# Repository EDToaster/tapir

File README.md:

# Keyboard projects

| Project | What it is | Status |
| --- | --- | --- |
| [Tapir](tapir/) | Flat wireless 42-key split keyboard with a thumb pointing stick | Rev A digital prototype, on hold |
| [TMR half](tmr-half/) | 28-key half-size analog keyboard with TMR sensors and rapid trigger | Rev A test coupon rebuilt for second review, not ordered |

Shared [silkscreen patterns](silkscreen-patterns/) hold generative artwork for any board here.

Each project has its own README and AGENTS.md. Run Tapir's commands from `tapir/`.

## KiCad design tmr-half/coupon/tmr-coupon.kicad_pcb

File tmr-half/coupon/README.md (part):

# TMR half test coupon, rev A

A 2 × 3 key test board for the [TMR half](../README.md) keyboard. It carries the same sensor cell, the same multiplexer and the same sensor power switch that the 28-key board would use, so the open questions in [design-decisions.md](../design-decisions.md) can be answered with measurements before the full board is drawn.

**Status: rev A rebuilt for second review; not ordered.** The CAD and CAM gates pass. Nothing has been measured on hardware. Ordering needs the owner's approval ([AGENTS.md](../AGENTS.md)).

The schematic is [tmr-coupon.kicad_sch](tmr-coupon.kicad_sch) ([picture](docs/schematic.png)). The board is [tmr-coupon.kicad_pcb](tmr-coupon.kicad_pcb). Both open in KiCad 10.

## What it tests

| Question | How the coupon answers it |
| --- | --- |
| How strong is the field at rest and at bottom-out? | Six sensor cells at the Partial-Gauss position. T1 compares 1.2 mm and 1.6 mm boards and checks the margin for 0.500 and 0.75 sensitivity. |
| Is the cheap 74HC4067 fast enough? | Both muxes are the CD74HC4067SM96 proposed in D7, wired the way the full board would be. |
| How much does the bypass capacitor matter? | Rail A (K1–K3) has the datasheet 100 nF per sensor. Rail B (K4–K6) has 10 nF. |
| Does the optional output capacitor help or hurt? | K2 and K5 have 100 pF on the sensor output. Their neighbours have empty pads. |
| What does pulsing the sensor power cost? | Each rail has a switch, a 10 Ω current shunt and a voltage monitor. T6 checks when a key reading becomes valid after power-on. |
| Does an RC filter in front of the ADC help? | 0 Ω links and empty capacitor pads sit at both ADC inputs. |
| Does the optional battery path work? | The JST-PH connector feeds the module's B+ pad through Q3 and a slide switch. A warning LED is connected on the battery side of both. |

## How the circuit works

A short tour for someone new to analog circuits.

- **Sensor cell.** Each key has one TMR2617S on the bottom of the board, 4.40 mm south of the switch centre. It has three pins: supply, ground, and an output voltage that moves as the magnet in the switch comes closer. A small capacitor next to it steadies its supply.
- **Multiplexer.** The controller only has three free analog inputs, so a 16:1 analog switch (U7, U8) picks one sensor at a time and connects it to one ADC pin. Four select lines S0–S3 carry a binary address from 0 to 15. Both muxes share the select lines, so both muxes present their selected inputs at once. The SAADC samples the two inputs sequentially.
- **Channel map.** Key inputs on each mux are separated by grounded inputs. Key and ground addresses: Addresses 1, 3 and 5 carry K1/K2/K3 on A and K4/K5/K6 on B. Addresses 0, 2, 4, 6 and 8–15 read ground. Rail-monitor addresses: Both monitors use address 7. Grounded addresses give a zero reading for offset and settling tests.
- **Rail switch.** Q1 and Q2 are P-channel MOSFETs between the module's 3.3 V pin and the two sensor rails. Each 100 kΩ gate pull-down keeps its rail on by default. A high on PWR_A_N or PWR_B_N turns that rail off.
- **Shunt.** Each rail has a 10 Ω current-sense resistor. A reading of 1 mV across it means 100 µA. The expected steady drop is up to about 11 mV: three sensors at up to 300 µA each plus 3.3 V / 20 kΩ = 165 µA for the monitor, or 1.065 mA × 10 Ω = 10.65 mV at nominal values ([MDT datasheet, p. 4](https://www.dowaytech.com/en/res/202408/21/dd53d68876041b0f.pdf), **drawing** plus calculation).
- **Rail monitor.** Two 10 kΩ resistors halve each sensor rail into its MON channel. Use the monitor from the same rail and ADC channel as the key. After subtracting the ground reading from each, divide the key reading by twice the MON reading to get Vout / Vsensor. Sample them close together with the rail on and stable. Skip the calculation if MON is near zero. See [Supply and reference](../analog-readout.md#supply-and-reference).
- **ADC filter pads.** R11 and R12 are 0 Ω links and C19 and C20 are empty. Swap in a resistor and capacitor to try a filter without a new board.

## Pin map

Controller pads as seen from the top with USB at the top edge. Pin names follow the [nice!nano v2 pinout](https://nicekeyboards.com/docs/nice-nano/pinout-schematic/).

| Signal | nRF pin | Pro Micro name | Notes |
| --- | --- | --- | --- |
| S0, S1, S2, S3 | P0.17, P0.20, P0.22, P0.24 | D2, D3, D4, D5 | Mux address, S0 is the low bit |
| MUX_EN_N | P1.00 | D6 | Low enables both muxes. Pulled low by R13, so it can be left alone. |
| PWR_A_N | P0.11 | D7 | High turns rail A off. Leave floating or low for always on. |
| PWR_B_N | P1.04 | D8 | High turns rail B off. Use standard drive and low-frequency switching per the [Nordic pin table](https://docs.nordicsemi.com/r/bundle/ps_nrf52840/page/pin.html) (**drawing**). |
| AIN_A | P0.02 / AIN0 | | Mux A output (K1–K3) |
| AIN_B | P0.29 / AIN5 | | Mux B output (K4–K6) |
| AIN_SPARE | P0.31 / AIN7 | | Only goes to J3 pin 8. Configure as an output driven low when unused. |
| VCC | 3.3 V pin | | Supplies the muxes and both rail switches |
| B+ | battery pin | RAW position | From J1 through Q3 and S1. Verify B+ on your actual clone. |

Debug header J3 is vertical, pad 1 nearest the top edge. In pad order: GND, 3V3, SWA (before A shunt), VSA (after A shunt), SWB, VSB, S0, A7, MXB, MXA. The labels are on the bottom.

J3 is an exposed bench header, without added ESD protection or a fuse. Clip ground first and attach insulated probes with power off. Do not bridge 3V3 or either rail to a mux output; never drive J3 pin 8 while P0.31 is driving it low. Rev A has no S0–S3 pulls. While those GPIOs are high-impedance (reset, bootloader, or sleep modes that release them), the mux channel is undefined and floating input levels can increase supply current. Drive the selects to a known level before sampling and park them before sleep if the GPIO state is retained. Full-board pull-downs are Proposed in D19.

## Layout

| Item | Value |
| --- | --- |
| Board | 92 × 50 mm, 2 layers, 2 mm corner radius (**drawing**). T1 compares nominal 1.2 mm and 1.6 mm. |
| Keys | 19.05 mm pitch, 3 columns × 2 rows |
| Assembled parts | One-sided assembly on the bottom. 42 placements. |
| Hand-fitted | Controller on the top, six switches pressed in from the top |
| Mounting | Four M2 holes at 3 mm from each corner |
| Antenna | No copper on either layer under the controller's antenna end |
| Battery | J1 opens toward the bottom edge. S1's lever extends 1.00 mm past the edge and its body stops 0.50 mm short (nominal drawing geometry). |
| Decoration | Quadtree Truchet pattern on both silkscreen layers, see [Decorative silkscreen](#decorative-silkscreen) |

Use the same design at both thicknesses for T1. Gateron shows the sensor under a 1.20 mm PCB beside a 1.20 ± 0.05 mm mechanical dimension ([KS-33D drawing, p. 7](https://www.gateron.com/u_file/2603/10/file/GATERONLowProfileMagneticJadeProSwitch-KS-33DD10B060NW-D276.pdf), **drawing**). JLCPCB's [rigid PCB capabilities](https://jlcpcb.com/capabilities/pcb-capabilities) list ±10% thickness tolerance at 1.0 mm and above, so measure the bare edge of each finished board. The switches use locating posts, the battery connector and slide switch are surface mounted, and ordinary soldered headers and M2 fasteners can be sized for either board. Dry-fit everything. Check that the switch bodies sit flat, header pins protrude far enough to solder, locator pegs do not foul the mounts and M2 screws engage without bottoming out. Retention without a plate is still untested.

Design rules used, against [JLCPCB's published limits](https://jlcpcb.com/capabilities/pcb-capabilities) for 2-layer 1 oz boards:

| Rule | This board | JLCPCB minimum |
| --- | --- | --- |
| Track width | 0.20 signal class, 0.40 power class, 0.15 absolute minimum; five signal segments below class width | 0.10 |
| Clearance | 0.20 | 0.10 |
| Via | 0.60 pad, 0.30 hole | 0.25 pad, 0.15 hole |
| Copper to board edge | 0.30 DRC; 0.4000 pour, 0.5273 track, 0.5350 via, 0.4350 pad (generated Gerber to routed centreline) | 0.20 fabrication; >0.30 for Economic assembly traces |
| Copper to unplated hole | 0.30 | 0.20 |
| Silkscreen text height | 1.0 | 1.0 |
| Silkscreen line width | 0.15 text strokes; 0.30 thinnest pattern feature | 0.15 |
| Silkscreen to pad | 0.30 for the pattern | 0.15 |

Round 2 reused the reviewed route, with no signal copper moved. The [analog layout report](reports/analog-layout.json) measures track and via proximity from 21 aggressors (address/control, reset, battery, rails, gates and MON), including MON and AIN_SPARE as victims. A sensor's own supply near its VCC pad is reported separately within a 1.5 mm escape radius (**allowance**). The existing rail/MON proximities, the 12.054 mm MUXB/RST and 5.239 mm OUT3/VCC opposite-layer parallel spans are retained and reported; do not sample during reset or VCC transitions. T2–T4 still have to measure the actual effect. These geometry checks are not a prediction of coupled noise.

In the close-track metric (**measured** by the repository gate from KiCad geometry), AIN_SPARE runs 2.221 mm within 0.50 mm of S1, at a minimum edge gap of 0.2105 mm. AIN_SPARE/MUXB have 0.648 mm of close same-layer run and a 0.2274 mm via proximity. MUXA/MUXB have no close same-layer track run, 0.744 mm of opposite-layer parallel overlap and a 0.3071 mm closest via proximity. These track/via numbers exclude component lands; the review's 5.7 mm segment tally near J3 and R11 is an upper bound, not projected parallel length.

Three nets meet the unchanged 80% opposite-layer ground coverage goal. The regression floors give roughly three percentage points of headroom below achieved coverage; they are not design targets.

| Net | Original coverage (%) | Rev A coverage (%) | Regression floor (%) |
| --- | ---: | ---: | ---: |
| OUT1 | 74.0 | 67.7 | 64 |
| OUT2 | 52.9 | 60.8 | 57 |
| OUT3 | 45.2 | 85.0 | 82 |
| OUT4 | 42.4 | 78.9 | 75 |
| OUT5 | 31.5 | 100.0 | 97 |
| OUT6 | 48.0 | 80.8 | 77 |
| MUXA | 55.3 | 47.2 | 44 |
| MUXB | 54.5 | 65.9 | 62 |
| AIN_A | 0.0 | 58.9 | 55 |
| AIN_B | 0.0 | 59.1 | 56 |

The generated board has 97 two-sided ground stitching vias, two front/eight back filled regions and at least two ties per region. All 17 critical ground pads touch local pour; their longest distance to a through stitch is 1.05 mm. Of 336.369 mm of retained GND trace, 44.313 mm of centreline lies outside a same-layer pour. The fill minimum is 0.20 mm on both layers; the first substantial split in the erosion screen is at 0.240 mm front and 0.200 mm back. These are CAD measurements and a geometry screen, not measurements of etching or electrical performance. T2 through T4 still need physical measurements.

The [mechanical report](reports/mechanical.json) measures 0.3058 mm from the closest sensor land to the Ø5.2 mm hole and a 0.40 mm minimum battery trace width on all three battery positive nets. Mux bypass supply pad centres are 1.75 mm apart; the corresponding ground pad centres are 12.578 mm apart. Both grounds reach local pour and stitching; those distances do not measure the electrical loop length.

## Parts

The full list with part numbers is [bom.csv](bom.csv). The files JLCPCB needs are in [fab/](fab).

| Refs | Part | LCSC | JLC class |
| --- | --- | --- | --- |
| U1–U6 | MDT TMR2617S-AAC-0.500-500, SOT-23-3 | [C55130211](https://www.lcsc.com/product-detail/C55130211.html) | Extended |
| U7, U8 | TI CD74HC4067SM96, SSOP-24 | [C98457](https://www.lcsc.com/product-detail/C98457.html) | Extended |
| Q1–Q3 | AO3401A P-MOSFET, SOT-23 | C15127 | Basic |
| J1 | JST S2B-PH-SM4-TB(LF)(SN) | C295747 | Extended |
| S1 | C&K PCM12SMTR, 300 mA at 6 V DC | [C221841](https://jlcpcb.com/partdetail/CK-PCM12SMTR/C221841) | Extended |
| D1 | KENTO KT-0603R red warning LED | [C2286](https://jlcpcb.com/partdetail/C2286) | Basic |
| R15 | 1 kΩ 0603WAF1001T5E | [C21190](https://jlcpcb.com/partdetail/C21190) | Basic |
| C1–C3, C7, C8 | 100 nF 0603 | C14663 | Basic |
| C4–C6 | 10 nF 0603 | C57112 | Basic |
| C12, C15, C17, C18 | 100 pF C0G 0603 | C14858 | Basic |
| C9 | 1 µF 0603 | C15849 | Basic |
| R1, R2 / R3, R4 / R5, R6 | 100 Ω / 100 kΩ / 10 Ω 0603 | C22775 / C25803 / C22859 | Basic |
| R7–R10, R13 / R11, R12 | 10 kΩ / 0 Ω 0603 | C25804 / C21189 | Basic |

Not fitted on purpose: C11, C13, C14, C16 (output capacitor positions) and C19, C20 (ADC filter capacitors). Paste intentionally remains on these pads for later hand fitting.

You supply and fit by hand:

- The nice!nano v2 clone.
- Six Gateron Low Profile Magnetic Jade Pro switches. [NuPhy](https://nuphy.com/products/gateron-low-profile-magnetic-jade-pro-switches) sells them in packs of 70 or 90.
- Four brass or nylon M2 standoffs and screws. Start with 8 mm or taller (**allowance**). Avoid steel near the magnets. From board coordinates, the nearest mounting hole is H1, 15.207 mm centre-to-centre from K1. The closest S1/J1 metal mounting-land centre is 18.742 mm from K6. This is a PCB measurement, not a magnetic field measurement.
- Optional: a 1-cell LiPo with a JST-PH plug such as [Adafruit 1578](https://www.adafruit.com/product/1578), keycaps, and a 10-pin header for J3.

### Sensor stock

On 2026-11-27, [JLCPCB C55130211](https://jlcpcb.com/partdetail/58850683-TMR2617S_AAC_0_500500/C55130211) showed zero stock, Extended, with a minimum buy of 18. At its displayed estimate of $0.5015 each, 18 cost about $9.03 before any fees or tax. [LCSC C55130211](https://www.lcsc.com/product-detail/C55130211.html) also showed out of stock, with minimum 1, multiple 1, and a reference price of $0.4989 for one. Recheck both listings and the price before buying.

For a fully assembled coupon, pre-order C55130211 in the JLCPCB Parts Library. Wait until your library shows enough available parts for the boards and any assembly allowance shown by JLCPCB. Each board uses six sensors. Eighteen pieces may be insufficient for two assembly orders. JLCPCB keeps pre-ordered parts for PCBA and does not ship them separately. Lead time is unconfirmed.

If you choose to hand-solder the sensors, deselect U1–U6 in the assembly BOM. Source the exact TMR2617S-AAC-0.500-500 from LCSC if it returns to stock, or verify the SOT-23-3 package, 0.500 mV/V/Gs sensitivity and 500 mV/V offset before using [Calero's programmed-to-order TMR2617S option](https://tmr-sensors.com/products/tmr2617). Confirm lead time and total cost before placing a board order. Pins 1 and 2 have 1.10 × 0.60 mm lands and 0.20 mm nominal toe. Pin 3 has a 1.45 × 0.60 mm land and 0.55 mm nominal toe. The toe is calculated from PCB dimensions and the MDT p. 6 lead span. Use a fine tip beside the center hole.

### Decorative silkscreen

Both sides carry a crop of the [quadtree Truchet pattern](../../silkscreen-patterns/) (pattern 03), enlarged so the lines print thicker. It is cosmetic and connects to nothing.

| Item | Value |
| --- | --- |
| Source | `silkscreen-patterns/svg/03_quadtree_truchet.svg`, 400 × 250 mm |
| Zoom | 2×, so the board shows a 46 × 25 mm window of the source |
| Window, top side | Top-left corner at (90, 95) mm in the source |
| Window, bottom side | Top-left corner at (300, 150) mm in the source |
| Stroke widths | 0.78, 1.56 and 2.80 mm (source strokes 0.39, 0.78 and 1.40 mm, **drawing**) |
| Ink | 247.5 mm² in 20 areas on top, 392.2 mm² in 24 areas on the bottom (generated-board measurement) |

Every functional mark takes priority over the pattern. [tools/silk_pattern.py](tools/silk_pattern.py) turns the strokes into filled areas and cuts away anything closer than these distances:

| Kept clear of | Distance (**allowance**) |
| --- | --- |
| Pads, holes, part courtyards and silkscreen lines | 0.30 mm |
| Text labels | 0.45 mm around the label's box |
| Board edge | 0.60 mm |
| M2 mounting holes | The 5.1 mm screw-head courtyard plus 0.30 mm, on both sides |

Gaps between keepouts narrower than 1.0 mm stay empty. Leftover pieces thinner than 0.30 mm, smaller than 4 mm² or shorter than 4.5 mm are dropped. [tools/check_silk.py](tools/check_silk.py) measures the decorative ink on the routed board: 0.299 mm from the closest pad, hole or mark (the 0.30 mm target less polygon rounding) and 0.625 mm from the board edge ([decoration report](reports/silk-clearance.json)). The plotted legend as a whole comes within 0.345 mm on top and 0.425 mm on the bottom ([Gerber read-back](reports/gerber-silk.json)).

Two things to know:

- The six front 14 × 14 mm seating squares exclude all legend ink. The LED cues are outside them.
- Vias are tented. The [silk read-back report](reports/gerber-silk.json) measures 10 via holes under plotted ink on the top and 18 on the bottom.

To change the look, edit `ZOOM` or `CROP` in `silk_pattern.py` and run `tools/build.sh`. Copper is untouched, so no reroute is needed.

## Ordering at JLCPCB

Wait for the owner's approval before buying anything. The proposed comparison is one assembled batch at nominal 1.2 mm and one at 1.6 mm. A cheaper option is one assembled thickness plus bare boards at the other thickness. Populate at least one bare board with the same parts and capacitor options before comparing. Choose at order time.

1. Upload `fab/tmr-coupon-revA-gerbers.zip` for each thickness. Confirm the detected 92 × 50 mm outline and two layers (**drawing**).
2. Set the chosen thickness. [JLCPCB Economic PCB Assembly capabilities](https://jlcpcb.com/capabilities/pcb-assembly-capabilities) list both thicknesses for a single board of this size. Choose green solder mask and explicitly select lead-free HASL if available for both thicknesses (Proposed); use the same finish and mask for the comparison. Choose “Order Number (Specify Position)” if using the bottom-side placeholder.
3. Turn on Economic PCB Assembly and select **Bottom Side** for the assembled batch or batches. Two or five boards per assembled batch fit the published two-layer green/HASL options.
4. Upload `fab/tmr-coupon-revA-bom-jlc.csv` and `fab/tmr-coupon-revA-cpl-jlc.csv`. Check the fitted lines match the exported BOM: 16 BOM lines.
5. For a complete assembly, stop unless the sensors are available in the JLCPCB parts library for your order. See [Sensor stock](#sensor-stock).
6. Inspect the placement preview before paying. Check mux pin 1 at the triangles, sensors and MOSFETs on the right pads, the warning LED polarity, and the J1 opening and S1 lever toward the edge. Confirm S1's two pegs centre over the two Ø0.90 mm holes and the sensor bodies centre 4.40 mm south of their switch centres (**drawing**). The offline CPL gate is not a substitute for this preview.
7. Account for the edge conflict. S1's body is 0.50 mm inside the nominal routed edge, but its lever overhangs by 1.00 mm; J1 mates toward the same edge. The [Economic FAQ](https://jlcpcb.com/help/article/pcb-assembly-faqs-part-2) asks for more than 0.30 mm clearance for traces and components and quotes about 0.20 mm routing tolerance; the [assembly terms](https://jlcpcb.com/help/article/terms-and-conditions-of-jlcpcb-assembly-service) call for at least 2.5 mm for component bodies. A copper-rule pass does not clear the assembly envelope. Plan for one of three outcomes: an engineering query/hold for Economic assembly, Standard assembly with removable rails and actuator clearance, or deselect S1 in the assembly order and hand-fit it after depaneling.
8. Review the tooling and final production file. The [after-sales FAQ](https://jlcpcb.com/help/article/common-pcba-after-sales-issues-and-faq) says Economic assembly typically adds two or three Ø1.152 mm NPTH tooling holes near the corners. Use blank corner locations where possible; corner copper is ground only, not a licence to cut a stitch, interfere with an M2 hole, or cut live copper elsewhere. Confirm the tooling holes, rails, fitted part list and placement/polarity in the live production file under Order History before release. Do not assume it matches the preview.

### Before you pay

- **Sensor supply:** Verify enough of C55130211 for the order and assembly allowance, or choose the documented hand-solder route. Do not rely on a stock snapshot.
- **Thickness:** Choose the D12 plan for the 1.2 mm and 1.6 mm comparison, with matching parts, mask and finish.
- **Edge assembly:** Accept the S1 overhang risk and choose an assembly fallback. Check the new tooling holes and how any rails clear the actuator and J1.
- **Battery:** Accept that reverse pack + USB + S1 on remains unprotected. Use the first-connection procedure each time and accept the Proposed D18 LED limitation separately.
- **Test firmware:** Plan the bare-metal T3/T6 timing test; it is not implemented, and the ZMK sketch does not replace it.
- **Clone checks:** Verify B+, VCC and P0.13 on the actual controller before soldering.
- **Placement:** Complete step 6, including both S1 pegs and all six sensor centres; confirm the final production file when available.
- **Ground reference:** Accept 47.2% under MUXA and 65.9% under MUXB as coupon limits, not full-board targets.
- **Extended fees:** Check the live quote for all four Extended lines (sensors, S1, muxes and J1). No fee amount has been verified.

## Assembly and bring-up

### Check your clone before soldering

1. Find the clone's B+ from its pinout or schematic. Compare the physical pad against the coupon footprint with USB pointing toward the same edge. Use continuity with all power removed if you need to confirm a connection. The RAW position alone does not identify a battery input.
2. Power the loose module from USB, with no battery. Measure its 3.3 V/VCC pin against GND and record the voltage. Keep the probes from bridging adjacent pads.
3. With test firmware on the loose module, drive P0.13 high and low and measure VCC in each state. ZMK's [genuine nice!nano v2 board file](https://github.com/zmkfirmware/zmk/blob/main/app/boards/nicekeyboards/nice_nano/nice_nano_nrf52840_zmk_2_0_0.overlay) enables VCC with P0.13 high (**drawing**). Verify your clone's behavior before using the pin. Leave external power enabled for the coupon. If B+ or VCC does not match the footprint, stop before soldering.

### Assembly

1. Inspect the bottom side. U7 and U8 pin 1 at the triangle. No solder bridges on the mux pins.
2. With nothing else attached, measure resistance between J3 pin 1 (GND) and pin 2 (3V3). It should not read as a short.
3. Solder the controller on the top side with its chips facing up and USB at the board edge. Pad 1 (square) is P0.06. Sockets or pin headers are fine.
4. Press the switches in from the top with the LED windows toward the LED marks. With no plate, the locating posts can let a switch lift or tilt. Keep each housing flat against the board, press straight down, and check that it returns to its seat. If needed, hold the housing down from its sides or tack it with removable tape away from the seating surface. Use the same method for both thicknesses.
5. Fit standoffs.
6. Plug in USB. Measure 3.3 V between GND and 3V3 on J3, and about 3.3 V on VSA and VSB.
7. Measure across each shunt from its switch side to its sensor side. Expect up to about 11 mV steady state with the rails on. See the shunt calculation above. On J3, measure SWA (3) minus VSA (4), or SWB (5) minus VSB (6).

### Optional battery

Use a compatible single-cell LiPo. Leave the module's charge-boost jumper open. The genuine nice!nano normally charges at about 100 mA and its boost setting is about 500 mA ([nice!nano FAQ](https://nicekeyboards.com/docs/nice-nano/faq/) and [battery guidance](https://nicekeyboards.com/docs/nice-nano/)). The [documented SuperMini version](https://wiki.icbbuy.com/doku.php?id=developmentboard:nrf52840) lists 100 mA normally and 300 mA with boost. Check both the module and the battery manufacturer's allowed charge current before using battery power. The switch is C&K PCM12SMTR, rated 300 mA at 6 V DC ([manufacturer datasheet, pp. 1–2](https://www.littelfuse.com/assetdocs/littelfuse-ck-slide-pcm-series-datasheet?assetguid=d2f6a96c-7a9a-4c4e-a5aa-4fe3075dffe5), **drawing**); 300 mA would use its entire current rating and 500 mA exceeds it. [JLCPCB C221841](https://jlcpcb.com/partdetail/CK-PCM12SMTR/C221841) showed 7,232 in stock, Extended, minimum one on 2026-11-27.

1. Unplug USB. Set S1 to OFF. Verify the lever positions at the switch terminals with continuity while the board is unpowered. Compare the loose pack contacts with the connector's `+` marking using a meter. JST-PH plugs come wired in both polarities ([SparkFun JST-PH guide](https://learn.sparkfun.com/tutorials/single-cell-lipo-battery-care/jst-ph-connectors)).
2. With USB still unplugged and S1 still OFF, plug in the pack. The reverse-polarity warning LED must stay dark. If it lights, unplug the pack and stop.
3. Confirm with a meter that J1 pin 1 is positive relative to board GND, using accessible pads or test points. A dark LED alone does not prove correct polarity. If the reading is missing, negative or unclear, unplug the pack and investigate. Switch on only after a positive meter reading.

To check that the `POLARITY` LED works, use no battery, unplug USB and set S1 OFF. Use a floating bench supply set to 3.0 V with a 3 mA current limit (**test allowance**). With its output off, connect supply positive to board GND (J1.2) and negative to J1.1. Briefly enable the output and verify that D1 lights; disable it and disconnect both leads before attaching a pack or USB. If it does not light, stop and inspect D1, R15 and the connections. Never intentionally reverse a real pack. A dark LED does not prove correct polarity: use the meter check above.

The D1 indicator (KT-0603R) anode goes to GND and its cathode goes through R15 (1 kΩ) to raw J1 pin 1. That lets it light with a reversed pack even while S1 is off. With a reversed 3.0–4.2 V pack the current is roughly 1–2.5 mA (estimate). A correctly connected fully charged 4.2 V pack reverse-biases D1 continuously, even with S1 OFF: 0.8 V below its 5 V absolute maximum, not a lifetime guarantee. [KENTO, pp. 2–3](https://www.lcsc.com/datasheet/lcsc_datasheet_1810231112_Hubei-KENTO-Elec-KT-0603R_C2286.pdf) specifies up to 5 µA reverse leakage at 5 V and 25 °C (**datasheet test condition**, not a measured 4.2 V drain or a hot limit). No extra diode in rev A. Continuous reverse bias, off-state drain and silent indicator failure are limits proposed for owner acceptance in D18.

| Pack and power state | Expected behavior |
| --- | --- |
| Correct pack, S1 on, USB absent | The pack starts powering the module through Q3's body diode. Q3 then turns on and carries the battery current with less voltage drop. |
| Correct pack, S1 on, USB present | The module can charge the pack through the turned-on Q3. Leave boost open and check the pack's allowed charging current. |
| Reversed pack, USB absent | Q3 normally blocks the negative pack voltage from B+. Its body diode is reverse-biased. The warning LED can light with S1 in either position. |
| Reversed pack, USB present, S1 off | S1's open throw isolates the charger B+ path. The raw-pack warning LED can still light. Do not intentionally test a reversed pack with USB attached. |
| Reversed pack, USB present, S1 on | The charger can raise B+ and turn Q3 on. Current can then flow from the charger through Q3 toward the reversed pack. The charger and the impedances of the module, pack and wiring affect that current. No safe current or Q3 dissipation can be claimed for this fault. |
| No pack, USB present | The module should run from USB. Keep S1 off before fitting a pack. With S1 on, some chargers may put voltage on the empty battery connector through Q3. |

Q3 is an AO3401A. Pin 1 is gate, pin 2 source and pin 3 drain; its body diode points from the raw-pack drain toward the switch-side source ([AOS datasheet, pp. 1–2](https://www.aosmd.com/sites/default/files/res/datasheets/AO3401A.pdf), **drawing**). Once on, a 3.0 V cell gives roughly −3.0 V gate-to-source drive. The datasheet specifies up to 85 mΩ at −2.5 V under its room-temperature test condition, equivalent to about 8.5 mV at 100 mA as a nominal design estimate. A 4.2 V cell gives about −4.2 V drive, inside the ±12 V absolute limit. The gate pull-down sets the DC voltage; its exact value mainly affects switching and susceptibility to leakage because a MOSFET gate draws little steady current.

## Test plan

These measurements are still to be made. Record the operator, instrument or firmware revision, supply, ADC settings, fitted capacitors, board thickness and raw data in [design-decisions.md](../design-decisions.md). Treat the numerical test thresholds below as **allowances**. Change them only with a recorded reason. Use settled readings as baselines and record raw counts as well as any corrected readings.

The proposed ZMK build in calibration mode can capture raw counts for T1, T2, T4 and T7. T5 needs a meter and T8 needs a meter and a running USB or ZMK build. A small bare-metal test build is needed for T3 and T6. It should use a timer or busy-wait for short delays, control the rail pins, and save samples in memory before printing. ZMK's mux driver sleeps between selecting and reading and has no rail-control output. USB-only serial logging cannot test battery-only operation; for T7 use battery-safe logging or meter readings of the settled mux outputs and their own rail voltages with USB removed.

| # | Test | Method | Pass or decision |
| --- | --- | --- | --- |
| T1 | Field, direction and board thickness | Measure finished board thickness with a caliper at an accessible bare edge. On each thickness, hold the switch housing flat and read every key at rest and bottomed, with the rail on. Check direction through the stroke. Let `q = Vout / Vsensor` from the same-rail monitor. Estimate field magnitude in gauss as `abs(q − 0.500) / 0.000500` using the nominal sensor calibration. Record the actual direction separately. | Readings change consistently through travel and keep margin from both output limits (approximately 5% and 95% of Vsensor, **drawing**). Compare worst endpoint and smallest travel swing by thickness. Use measured margin to judge whether 0.75 is viable and set `switch-pressed-is-higher` from measured direction. |
| T2 | Noise | Log 1,000 settled samples per key at rest. Compare 100 nF and 10 nF rails, and each 100 pF output-capacitor key with neighbours. Report peak-to-peak and RMS counts, with and without averaging. | Choose the smallest averaging window and capacitor option that keep the observed peak-to-peak noise below half the smallest intended trigger step in counts. Measure scan time with that window. If the trigger step is still unknown, report the minimum defensible step and leave this pass open. |
| T3 | Mux settling | On each mux alternate directly between a bottomed key and an unpressed key at clearly different readings. Separately alternate between a key and a grounded input. Test both directions and the keys with and without the 100 pF output capacitor. Busy-wait after the last address GPIO changes, then trigger the ADC. Sweep from 20 µs down to 1 µs, with a longer reference delay that gives stable readings. Keep ADC acquisition and key positions fixed. | The shortest delay whose repeated mean is within 2 ADC counts of each settled destination in both directions and that adds no repeatable dependence on the previous channel is usable, provided the resulting scan with T2's averaging fits the scan budget. Report noise and uncertainty; if they hide a 2-count shift, the result is inconclusive. |
| T4 | Neighbour crosstalk | Press one key fully while logging each nearest neighbour with its housing held flat. Repeat using a long settle delay to minimise mux history. Compare with T2's idle data. | Repeatable neighbour shifts stay below half the smallest intended trigger step, with noise accounted for. Otherwise estimate the required compensation or revise spacing, retention or layout. |
| T5 | Rail current | With the rails on and settled, measure across both shunts. Multiply millivolts by 100 µA/mV. Subtract the measured rail voltage / 20 kΩ to estimate the current of the three sensors alone. | Results are consistent with up to about 11 mV across each shunt at 3.3 V and up to 900 µA for three sensors, allowing for meter, resistor and supply tolerances. |
| T6 | Pulsed rail and sensor readiness | On each rail, hold one key at rest, then repeat bottomed. Record the long-on baseline. Start each trial from a repeatable off interval and verify the rail discharges as intended. With sampling stopped and S0–S3 low, switch on the rail, select the test key, and trigger its first ADC acquisition at a known time from the rail-enable edge. Try 20 µs steps to 200 µs, then extend or refine the sweep as needed. Repeat each delay from power-off. Scope the rail at J3 if available and repeat with MON as a separate trace. | Use the earliest delay at which the repeated mean key reading and its noise meet the settled T3 and T2 limits at that and all later tested delays. Document supply and bypass values. Pulse only if the measured current savings are useful and wake time plus the measured scan fits the intended interval. |
| T7 | Supply sensitivity | Keep a key fixed and compare stable USB-only and verified battery-only operation. Compare raw key readings, raw MON readings and the corrected key-to-rail ratio. If using a meter, park the mux on the key and measure its output and Vsensor against GND. | The corrected position stays within the T2 step budget across the tested supplies. Report how much the correction helps and the actual voltages tested. |
| T8 | Battery path | Follow the first-connection procedure. With correctly wired pack and USB unplugged, check that S1 enables pack operation and OFF stops it. Confirm USB-only operation with the pack disconnected. Then check for charging with the correctly wired, partly discharged pack and S1 on. Verify charge indication or measured charge current without shorting the pack; leave boost open. | Each power mode works as expected; observed charge current is within both the module/switch rating and the pack's charge limit. The warning LED is dark with the correctly wired pack. Never test a reversed pack with USB attached. |

For T6, the rail and sensor have separate settling times. Using the nominal three sensor bypass capacitors and the roughly 10 Ω shunt-plus-FET path, the simple rail RC estimate is about 3 µs with 100 nF per sensor and 0.3 µs with 10 nF per sensor. The MON divider's 5 kΩ effective output resistance and 100 pF capacitor add about 0.5 µs. These are estimates; the FET's gate transition, loading and the ADC acquisition affect the measured result. The sensor datasheet gives 100 µs maximum power-on time (MDT p. 4, **drawing**). MON can show that the rail voltage has recovered; it cannot show that a key reading has settled. Use a scope for the rail edge itself.

Before switching a sensor rail or the module's 3.3 V supply off, stop ADC sampling and drive S0–S3 low. Keep sampling stopped while the relevant supply is off. Re-enable power before selecting a key and resume readings after the measured wake delay. Leave the mux on its 3.3 V supply when pulsing a sensor rail. If the overall 3.3 V supply is off, keep other signals that reach the mux low or otherwise inactive as well. This avoids feeding unpowered circuitry through a signal pin. See [Circuit rules](../analog-readout.md#circuit-rules-for-the-schematic).

## ZMK starting point

A sketch for [zmk-feature-hall-effect](https://github.com/cr3eperall/zmk-feature-hall-effect) written from its `he,kscan-multiplexer` binding at commit 5ecb125. A stubbed devicetree syntax check is not a Zephyr binding or firmware build; the sketch has not been run.

```dts
/* NRF_SAADC_AIN* comes from <dt-bindings/adc/nrf-adc.h> or nrf-saadc-v3.h, depending on the Zephyr version ZMK pins. */
/* In firmware initialization, drive unused P0.31 (AIN_SPARE/J3.8) low as a GPIO output; do not bind it as an ADC input. */

&adc {
    status = "okay";
    #address-cells = <1>;
    #size-cells = <0>;
    channel@0 {                               /* AIN_A, mux A */
        reg = <0>;
        zephyr,gain = "ADC_GAIN_1_4";
        zephyr,reference = "ADC_REF_VDD_1_4"; /* Full scale follows MCU VDD. Correct with the same-rail MON reading. */
        zephyr,acquisition-time = <ADC_ACQ_TIME(ADC_ACQ_TIME_MICROSECONDS, 10)>;
        zephyr,input-positive = <NRF_SAADC_AIN0>;
        zephyr,resolution = <12>;
    };
    channel@5 {                               /* AIN_B, mux B */
        reg = <5>;
        zephyr,gain = "ADC_GAIN_1_4";
        zephyr,reference = "ADC_REF_VDD_1_4";
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
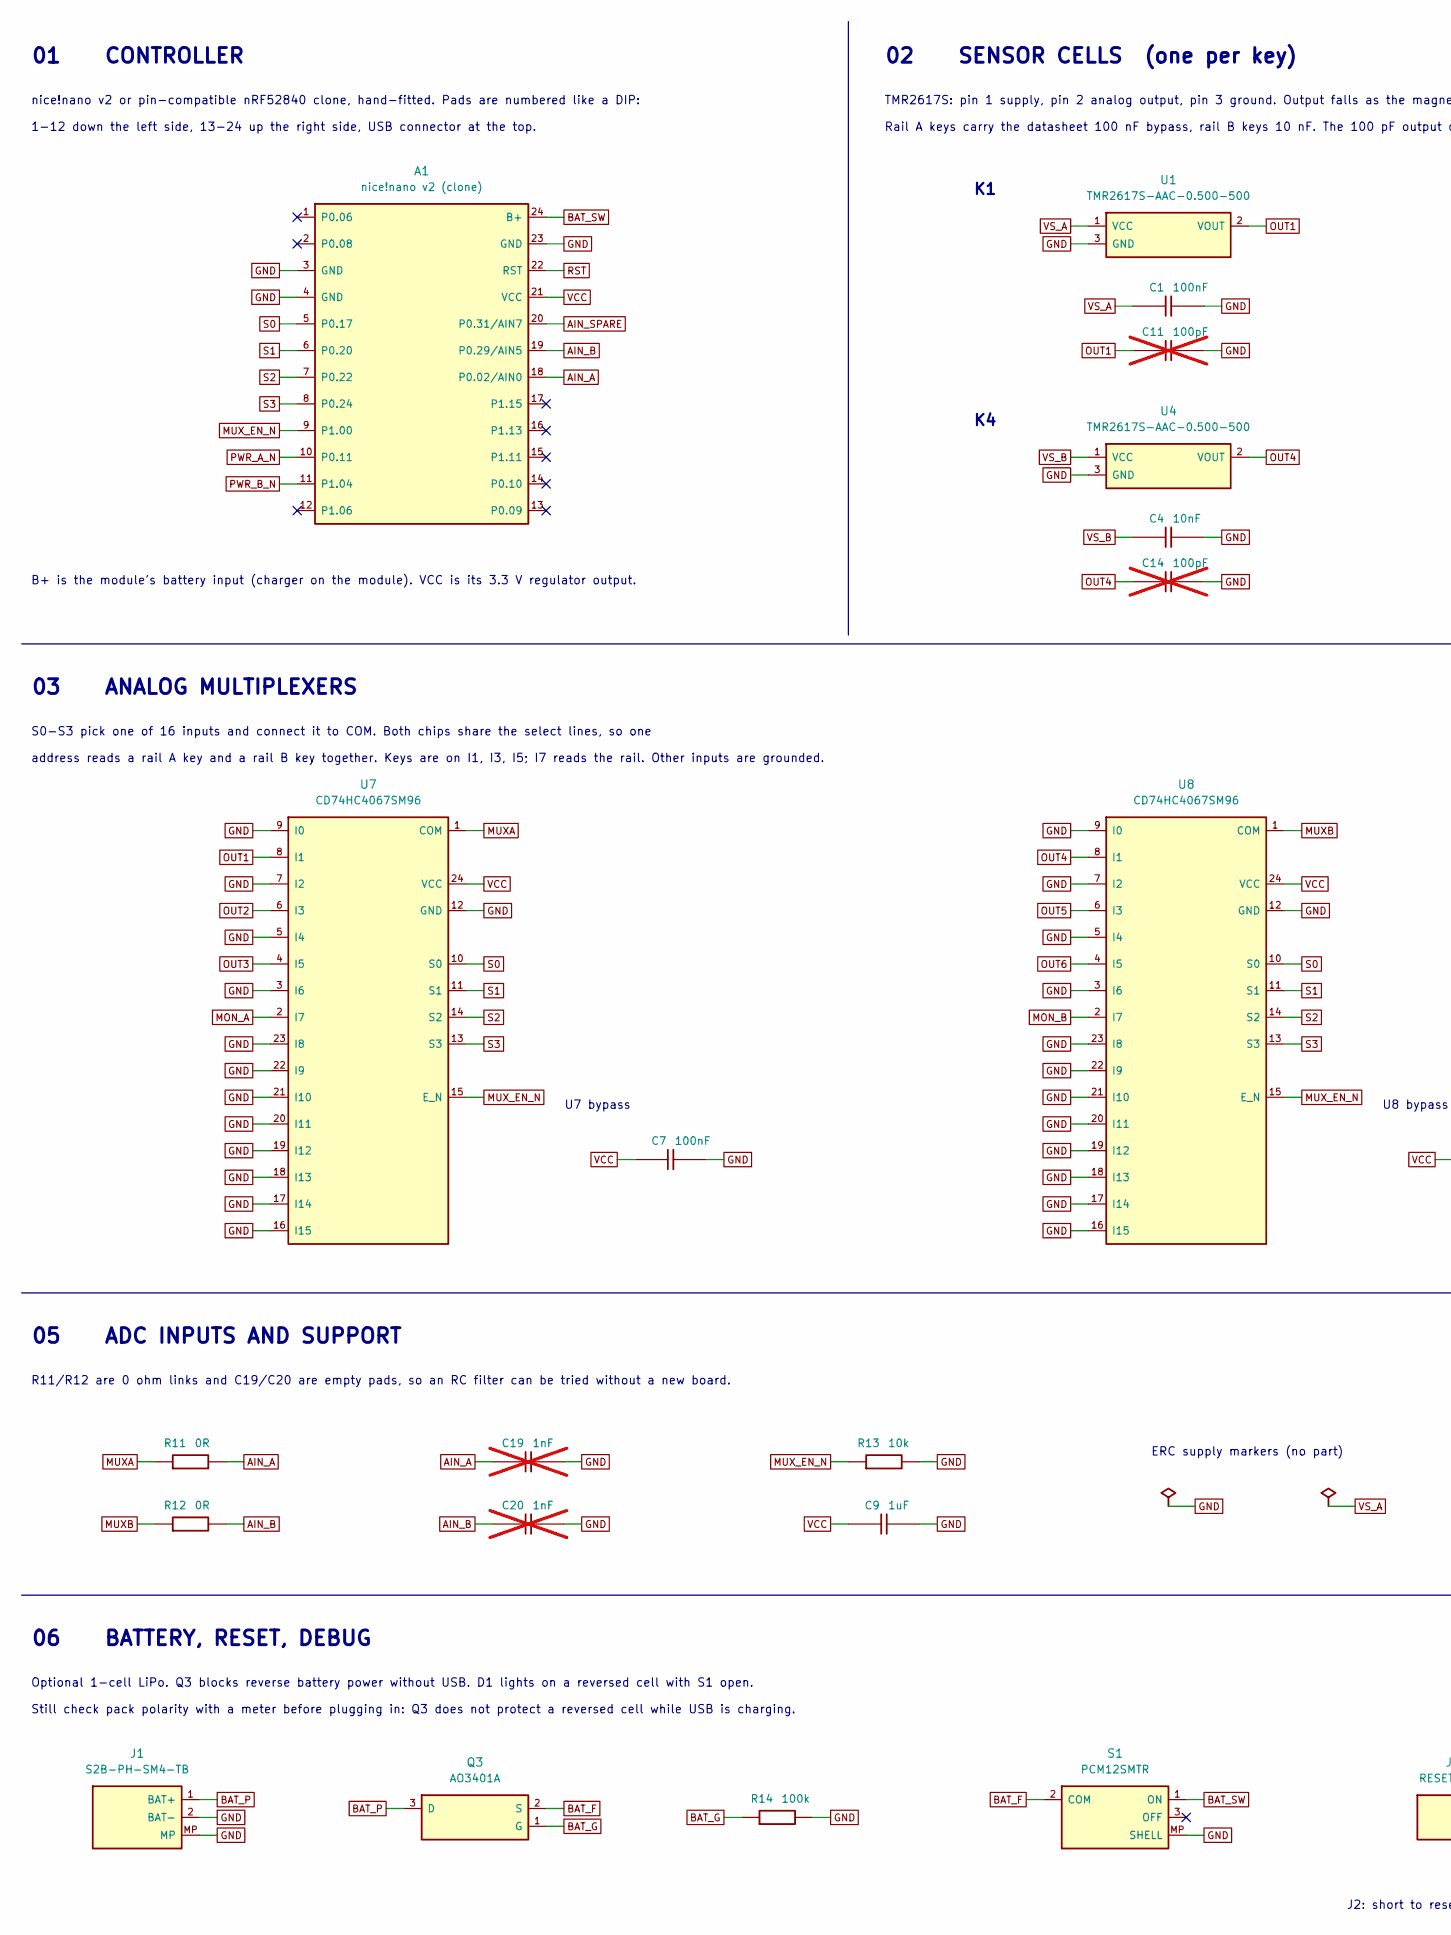
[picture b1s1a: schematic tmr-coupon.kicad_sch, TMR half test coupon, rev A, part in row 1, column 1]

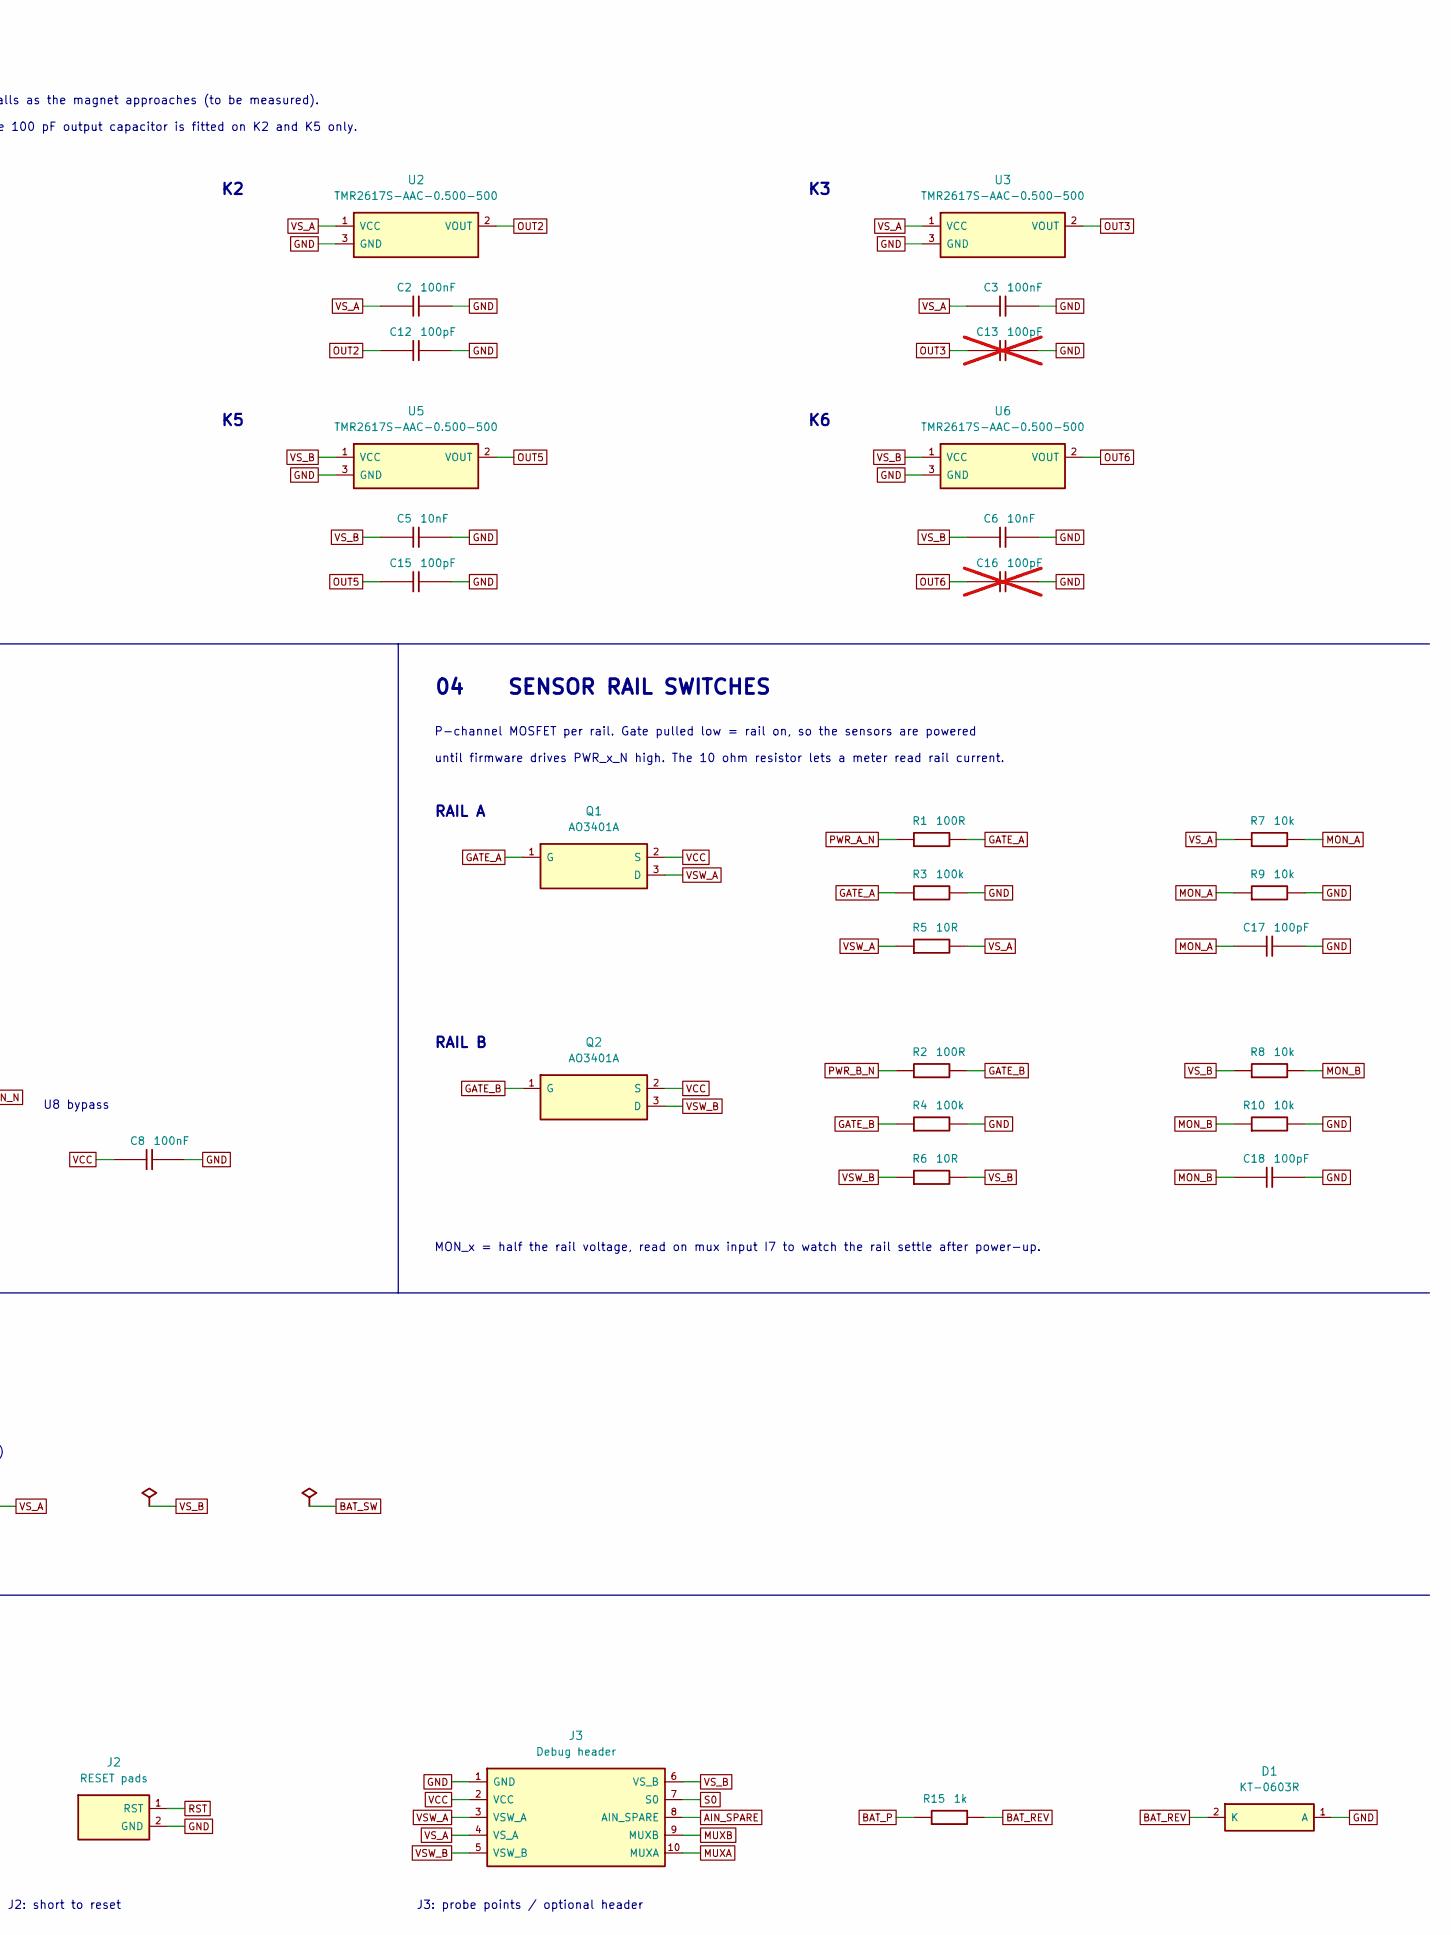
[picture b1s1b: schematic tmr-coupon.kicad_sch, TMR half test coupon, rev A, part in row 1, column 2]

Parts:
A1: nice!nano v2 (clone); ProMicro_nRF52840_THT
C1, C2, C3, C7, C8: 100nF; C_0603_1608Metric; MPN CC0603KRX7R9BB104; LCSC C14663
C4, C5, C6: 10nF; C_0603_1608Metric; MPN 0603B103K500NT; LCSC C57112
C9: 1uF; C_0603_1608Metric; MPN CL10A105KB8NNNC; LCSC C15849
C11, C13, C14, C16: 100pF; C_0603_1608Metric; MPN CL10C101JB8NNNC; LCSC C14858; not fitted
C12, C15, C17, C18: 100pF; C_0603_1608Metric; MPN CL10C101JB8NNNC; LCSC C14858
C19, C20: 1nF; C_0603_1608Metric; not fitted
D1: KT-0603R; LED_KENTO_KT-0603R; MPN KT-0603R; LCSC C2286
J1: S2B-PH-SM4-TB; JST_PH_S2B-PH-SM4-TB_1x02-1MP_P2.00mm_Horizontal; MPN S2B-PH-SM4-TB(LF)(SN); LCSC C295747
J2: RESET pads; PinHeader_1x02_P2.54mm
J3: Debug header; PinHeader_1x10_P2.54mm
Q1, Q2, Q3: AO3401A; SOT-23; MPN AO3401A; LCSC C15127
R1, R2: 100R; R_0603_1608Metric; MPN 0603WAF1000T5E; LCSC C22775
R3, R4, R14: 100k; R_0603_1608Metric; MPN 0603WAF1003T5E; LCSC C25803
R5, R6: 10R; R_0603_1608Metric; MPN 0603WAF100JT5E; LCSC C22859
R7, R8, R9, R10, R13: 10k; R_0603_1608Metric; MPN 0603WAF1002T5E; LCSC C25804
R11, R12: 0R; R_0603_1608Metric; MPN 0603WAF0000T5E; LCSC C21189
R15: 1k; R_0603_1608Metric; MPN 0603WAF1001T5E; LCSC C21190
S1: PCM12SMTR; SW_SPDT_CK_PCM12SMTR; MPN PCM12SMTR; LCSC C221841
U1, U2, U3, U4, U5, U6: TMR2617S-AAC-0.500-500; SOT-23-3_TMR2617S; MPN TMR2617S-AAC-0.500-500; LCSC C55130211
U7, U8: CD74HC4067SM96; SSOP-24_5.3x8.2mm_P0.65mm; MPN CD74HC4067SM96; LCSC C98457

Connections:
AIN_A: A1.18 (P0.02/AIN0), C19.1, R11.2
AIN_B: A1.19 (P0.29/AIN5), C20.1, R12.2
AIN_SPARE: A1.20 (P0.31/AIN7), J3.8 (AIN_SPARE)
BAT_F: Q3.2 (S), S1.2 (COM)
BAT_G: Q3.1 (G), R14.1
BAT_P: J1.1 (BAT+), Q3.3 (D), R15.1
BAT_REV: D1.2 (K), R15.2
BAT_SW: A1.24 (B+), S1.1 (ON)
GATE_A: Q1.1 (G), R1.2, R3.1
GATE_B: Q2.1 (G), R2.2, R4.1
GND: A1.3 (GND), A1.4 (GND), A1.23 (GND), C1.2, C2.2, C3.2, C4.2, C5.2, C6.2, C7.2, C8.2, C9.2, C11.2, C12.2, C13.2, C14.2, C15.2, C16.2, C17.2, C18.2, C19.2, C20.2, D1.1 (A), J1.2 (BAT-), J1.MP, J2.2 (GND), J3.1 (GND), R3.2, R4.2, R9.2, R10.2, R13.2, R14.2, S1.MP (SHELL), U1.3 (GND), U2.3 (GND), U3.3 (GND), U4.3 (GND), U5.3 (GND), U6.3 (GND), U7.3 (I6), U7.5 (I4), U7.7 (I2), U7.9 (I0), U7.12 (GND), U7.16 (I15), U7.17 (I14), U7.18 (I13), U7.19 (I12), U7.20 (I11), U7.21 (I10), U7.22 (I9), U7.23 (I8), U8.3 (I6), U8.5 (I4), U8.7 (I2), U8.9 (I0), U8.12 (GND), U8.16 (I15), U8.17 (I14), U8.18 (I13), U8.19 (I12), U8.20 (I11), U8.21 (I10), U8.22 (I9), U8.23 (I8)
MON_A: C17.1, R7.2, R9.1, U7.2 (I7)
MON_B: C18.1, R8.2, R10.1, U8.2 (I7)
MUXA: J3.10 (MUXA), R11.1, U7.1 (COM)
MUXB: J3.9 (MUXB), R12.1, U8.1 (COM)
MUX_EN_N: A1.9 (P1.00), R13.1, U7.15 (E_N), U8.15 (E_N)
OUT1: C11.1, U1.2 (VOUT), U7.8 (I1)
OUT2: C12.1, U2.2 (VOUT), U7.6 (I3)
OUT3: C13.1, U3.2 (VOUT), U7.4 (I5)
OUT4: C14.1, U4.2 (VOUT), U8.8 (I1)
OUT5: C15.1, U5.2 (VOUT), U8.6 (I3)
OUT6: C16.1, U6.2 (VOUT), U8.4 (I5)
PWR_A_N: A1.10 (P0.11), R1.1
PWR_B_N: A1.11 (P1.04), R2.1
RST: A1.22 (RST), J2.1 (RST)
S0: A1.5 (P0.17), J3.7 (S0), U7.10 (S0), U8.10 (S0)
S1: A1.6 (P0.20), U7.11 (S1), U8.11 (S1)
S2: A1.7 (P0.22), U7.14 (S2), U8.14 (S2)
S3: A1.8 (P0.24), U7.13 (S3), U8.13 (S3)
VCC: A1.21 (VCC), C7.1, C8.1, C9.1, J3.2 (VCC), Q1.2 (S), Q2.2 (S), U7.24 (VCC), U8.24 (VCC)
VSW_A: J3.3 (VSW_A), Q1.3 (D), R5.1
VSW_B: J3.5 (VSW_B), Q2.3 (D), R6.1
VS_A: C1.1, C2.1, C3.1, J3.4 (VS_A), R5.2, R7.1, U1.1 (VCC), U2.1 (VCC), U3.1 (VCC)
VS_B: C4.1, C5.1, C6.1, J3.6 (VS_B), R6.2, R8.1, U4.1 (VCC), U5.1 (VCC), U6.1 (VCC)

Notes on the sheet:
01 CONTROLLER
nice!nano v2 or pin-compatible nRF52840 clone, hand-fitted. Pads are numbered like a DIP:
1-12 down the left side, 13-24 up the right side, USB connector at the top.
B+ is the module's battery input (charger on the module). VCC is its 3.3 V regulator output.
02 SENSOR CELLS (one per key)
TMR2617S: pin 1 supply, pin 2 analog output, pin 3 ground. Output falls as the magnet approaches (to be measured).
Rail A keys carry the datasheet 100 nF bypass, rail B keys 10 nF. The 100 pF output capacitor is fitted on K2 and K5 only.
03 ANALOG MULTIPLEXERS
S0-S3 pick one of 16 inputs and connect it to COM. Both chips share the select lines, so one
address reads a rail A key and a rail B key together. Keys are on I1, I3, I5; I7 reads the rail. Other inputs are grounded.
U7 bypass
U8 bypass
04 SENSOR RAIL SWITCHES
P-channel MOSFET per rail. Gate pulled low = rail on, so the sensors are powered
until firmware drives PWR_x_N high. The 10 ohm resistor lets a meter read rail current.
RAIL A
RAIL B
MON_x = half the rail voltage, read on mux input I7 to watch the rail settle after power-up.
05 ADC INPUTS AND SUPPORT
R11/R12 are 0 ohm links and C19/C20 are empty pads, so an RC filter can be tried without a new board.
ERC supply markers (no part)
06 BATTERY, RESET, DEBUG
Optional 1-cell LiPo. Q3 blocks reverse battery power without USB. D1 lights on a reversed cell with S1 open.
Still check pack polarity with a meter before plugging in: Q3 does not protect a reversed cell while USB is charging.
J2: short to reset
J3: probe points / optional header

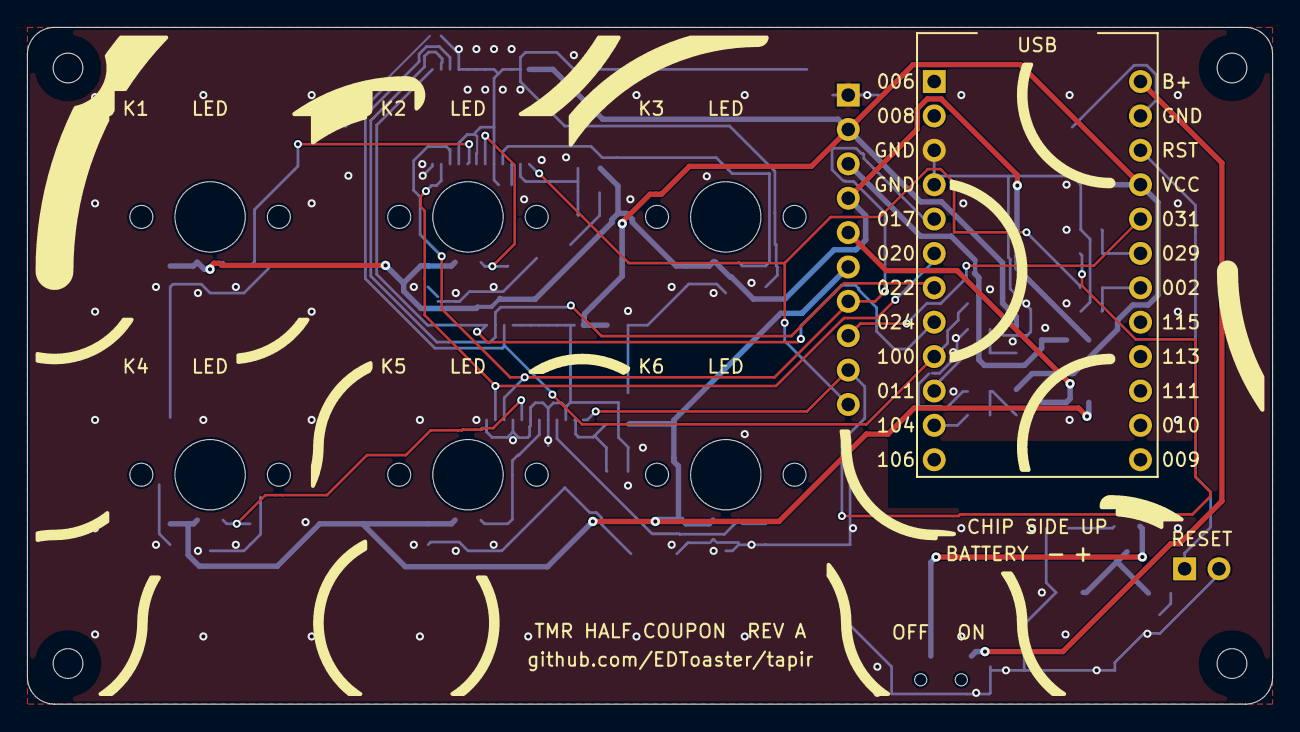
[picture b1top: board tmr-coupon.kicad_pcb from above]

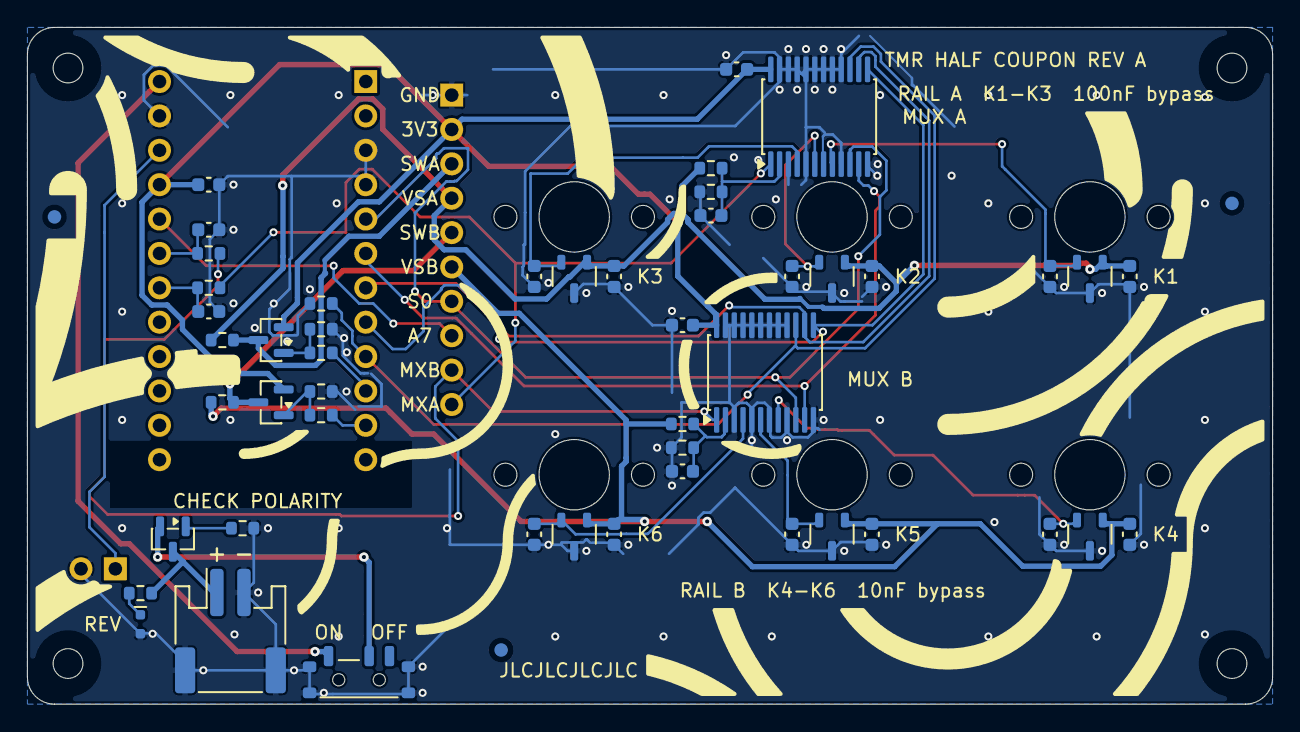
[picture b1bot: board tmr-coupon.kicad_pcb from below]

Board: 2 copper layers, 92.0 x 50.0 mm, 64 parts (51 on the bottom side), 34 nets.

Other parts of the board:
FID1, FID2, FID3: Fiducial_1mm_Mask2mm
H1, H2, H3, H4: MountingHole_M2_NPTH
SW1, SW2, SW3, SW4, SW5, SW6: SW_Gateron_LP_Magnetic_KS-33D

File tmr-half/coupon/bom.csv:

Refs,Qty,Value,Part number,Manufacturer,Footprint,LCSC,JLC class,Fit,Notes,Listing
"C1,C2,C3,C7,C8",5,100nF,CC0603KRX7R9BB104,YAGEO,C_0603_1608Metric,C14663,Basic,JLCPCB assembly,100 nF 50 V X7R 0603,https://www.lcsc.com/product-detail/C14663.html
"C4,C5,C6",3,10nF,0603B103K500NT,Fenghua (FH),C_0603_1608Metric,C57112,Basic,JLCPCB assembly,10 nF 50 V X7R 0603,https://www.lcsc.com/product-detail/C57112.html
C9,1,1uF,CL10A105KB8NNNC,Samsung Electro-Mechanics,C_0603_1608Metric,C15849,Basic,JLCPCB assembly,1 uF 50 V X5R 0603,https://www.lcsc.com/product-detail/C15849.html
"C12,C15,C17,C18",4,100pF,CL10C101JB8NNNC,Samsung Electro-Mechanics,C_0603_1608Metric,C14858,Basic,JLCPCB assembly,100 pF 50 V C0G 0603,https://www.lcsc.com/product-detail/C14858.html
D1,1,KT-0603R,KT-0603R,Hubei KENTO,LED_KENTO_KT-0603R,C2286,Basic,JLCPCB assembly,"KENTO red reverse-battery LED, 0603",https://www.lcsc.com/product-detail/C2286.html
J1,1,S2B-PH-SM4-TB,S2B-PH-SM4-TB(LF)(SN),JST,JST_PH_S2B-PH-SM4-TB_1x02-1MP_P2.00mm_Horizontal,C295747,Extended,JLCPCB assembly,JST PH 2-pin side-entry battery connector,https://www.lcsc.com/product-detail/C295747.html
"Q1,Q2,Q3",3,AO3401A,AO3401A,Alpha & Omega,SOT-23,C15127,Basic,JLCPCB assembly,"P-channel MOSFET, SOT-23",https://www.lcsc.com/product-detail/C15127.html
"R1,R2",2,100R,0603WAF1000T5E,UNI-ROYAL,R_0603_1608Metric,C22775,Basic,JLCPCB assembly,100 ohm 1% 0603,https://www.lcsc.com/product-detail/C22775.html
"R3,R4,R14",3,100k,0603WAF1003T5E,UNI-ROYAL,R_0603_1608Metric,C25803,Basic,JLCPCB assembly,100 kohm 1% 0603,https://www.lcsc.com/product-detail/C25803.html
"R5,R6",2,10R,0603WAF100JT5E,UNI-ROYAL,R_0603_1608Metric,C22859,Basic,JLCPCB assembly,10 ohm 1% 0603,https://www.lcsc.com/product-detail/C22859.html
"R7,R8,R9,R10,R13",5,10k,0603WAF1002T5E,UNI-ROYAL,R_0603_1608Metric,C25804,Basic,JLCPCB assembly,10 kohm 1% 0603,https://www.lcsc.com/product-detail/C25804.html
"R11,R12",2,0R,0603WAF0000T5E,UNI-ROYAL,R_0603_1608Metric,C21189,Basic,JLCPCB assembly,0 ohm 0603,https://www.lcsc.com/product-detail/C21189.html
R15,1,1k,0603WAF1001T5E,UNI-ROYAL,R_0603_1608Metric,C21190,Basic,JLCPCB assembly,1 kohm 1% 0603,https://www.lcsc.com/product-detail/C21190.html
S1,1,PCM12SMTR,PCM12SMTR,C&K,SW_SPDT_CK_PCM12SMTR,C221841,Extended,JLCPCB assembly,"C&K SPDT slide switch, side actuated, 0.3 A 6 V DC",https://www.lcsc.com/product-detail/C221841.html
"U1,U2,U3,U4,U5,U6",6,TMR2617S-AAC-0.500-500,TMR2617S-AAC-0.500-500,MultiDimension (MDT),SOT-23-3_TMR2617S,C55130211,Extended,JLCPCB assembly,"MDT linear TMR sensor, SOT-23-3",https://www.lcsc.com/product-detail/C55130211.html
"U7,U8",2,CD74HC4067SM96,CD74HC4067SM96,Texas Instruments,SSOP-24_5.3x8.2mm_P0.65mm,C98457,Extended,JLCPCB assembly,"TI 16:1 analog multiplexer, SSOP-24",https://www.lcsc.com/product-detail/C98457.html
"C11,C13,C14,C16",4,100pF,,,C_0603_1608Metric,,,Not fitted (DNP),100 pF 50 V C0G 0603,
"C19,C20",2,1nF,,,C_0603_1608Metric,,,Not fitted (DNP),"Optional ADC input capacitor, not fitted",
A1,1,nRF52840 Pro Micro-format controller,nice!nano v2 or pin-compatible clone,owner supplied,,,,Hand-fitted,"Hand-solder on the top side, chip side up, USB at the board edge. Sockets are fine.",
SW1-SW6,6,Low-profile magnetic switch,Gateron Low Profile Magnetic Jade Pro (KS-33D),Gateron,,,,Hand-fitted,Sold in packs of 70 or 90. Press-fit into the board holes; nothing is soldered.,https://nuphy.com/products/gateron-low-profile-magnetic-jade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
,6,Keycap,"Low-profile MX-stem keycap, 1u",any,,,,Hand-fitted,Optional for the measurements.,
BT1,1,1-cell LiPo with JST-PH plug,Adafruit 1578 (3.7 V 500 mAh),Adafruit,,,,Hand-fitted,Optional. Check plug polarity against the board silk with a meter first.,https://www.adafruit.com/product/1578
H1-H4,4,"M2 standoff, 8 mm or taller, with screws",,any,,,,Hand-fitted,Use brass or nylon near the magnets.,
J3,1,"1x10 pin header, 2.54 mm",,any,,,,Hand-fitted,"Optional, for a logic analyser or scope.",
